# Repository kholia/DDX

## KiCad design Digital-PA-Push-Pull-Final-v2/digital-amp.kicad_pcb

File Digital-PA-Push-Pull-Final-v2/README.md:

# Digital-PA

A digital mode power amplifier for 160-10m.
Created using Kicad 8.x.

Licensed under Attribution-NonCommercial 4.0 (CC BY-NC 4.0).

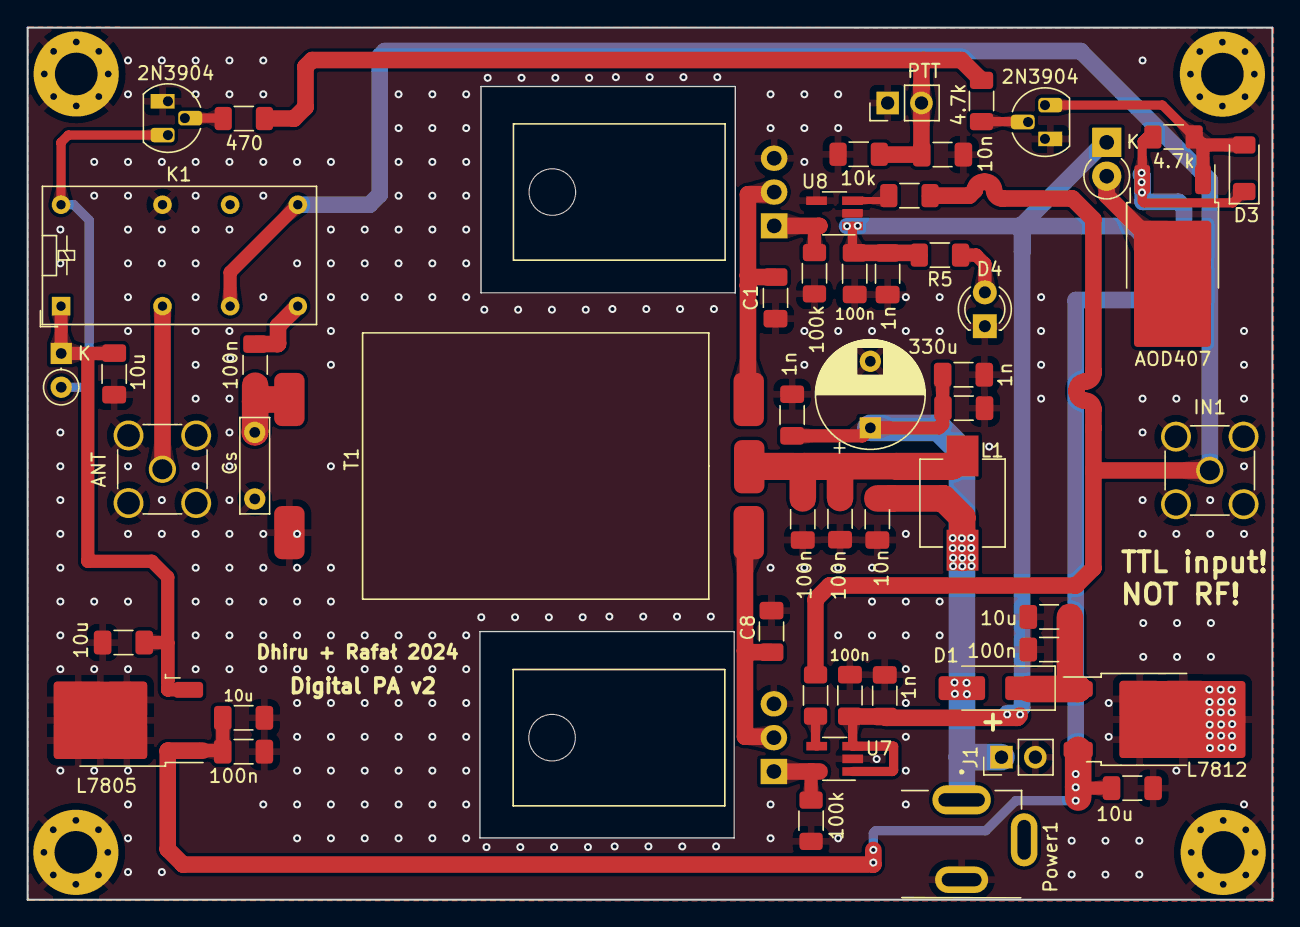
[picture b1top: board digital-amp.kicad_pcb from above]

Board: 2 copper layers, 93.5 x 65.5 mm, 58 parts (0 on the bottom side), 24 nets.

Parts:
B1, B2, B3, B4, B5: 100n; C_1206_3216Metric_Pad1.33x1.80mm_HandSolder
C1, C8: 100p; C_1206_3216Metric_Pad1.33x1.80mm_HandSolder
C2, C3, C5, C9, C11: 10u; C_1206_3216Metric_Pad1.33x1.80mm_HandSolder
C4, C6: 100n; C_1206_3216Metric_Pad1.33x1.80mm_HandSolder
C7: 330u; CP_Radial_D8.0mm_P5.00mm
C10: Cs; C_Rect_L7.0mm_W2.0mm_P5.00mm
C12, C13, C15, C17: 1n; C_1206_3216Metric_Pad1.33x1.80mm_HandSolder
C14, C16, C18: 10n; C_1206_3216Metric_Pad1.33x1.80mm_HandSolder
D1: SS54; D_SMA_Handsoldering
D2: 1N4148; D_DO-35_SOD27_P2.54mm_Vertical_KathodeUp
D3: 5.1V; D_MiniMELF
D4: LED_3mm; LED_D3.0mm
D5: 1N4007; D_DO-41_SOD81_P2.54mm_Vertical_KathodeUp
H1, H2, H3, H4: MountingHole_Pad; MountingHole_3.2mm_M3_Pad_Via
IN1: Conn_Coaxial; SMA_Amphenol_901-144_Vertical
J1: FAN; PinHeader_1x02_P2.54mm_Vertical
K1: Omron G5V-2 / OEN 46-05-2C; Relay_DPDT_Omron_G5V-2
L1: ASPI-0630LR-2R2; L_6.3x6.3_H3-Longer
PTT1: PTT; PinHeader_1x02_P2.54mm_Vertical
Power1: DC-005 (Barrel Jack); XKB_DC-005-5A-2.0_Modded
Q1: AOD407; TO-252-2-Mod
Q2, Q5: 2N3904; TO-92_HandSolder
Q3, Q4: IRF510; TO-220-3_Horizontal_TabDown
R1, R2: 100k; R_1206_3216Metric_Pad1.30x1.75mm_HandSolder
R3, R4: 4.7k; R_1206_3216Metric_Pad1.30x1.75mm_HandSolder
R5: 2k; R_1206_3216Metric_Pad1.30x1.75mm_HandSolder
R6: 470; R_1206_3216Metric_Pad1.30x1.75mm_HandSolder
R7: 10k; R_1206_3216Metric_Pad1.30x1.75mm_HandSolder
R8, R9: 3.3; R_1206_3216Metric_Pad1.30x1.75mm_HandSolder
RF1: ANT; SMA_Amphenol_901-144_Vertical
T1: BN-43-3312, 1T+1T:3T; BN-43-3312-Modded
U2: L7812; TO-252-2-Mod
U6: L7805; TO-252-2
U7, U8: UCC27517A; SOT-23-5_HandSoldering

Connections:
11.5V: B1.2, B2.2, C12.1, C13.1, D5.1 (K), R5.2, U7.1 (VDD), U7.3, U8.1 (VDD)
+5V: C3.1, C11.1, D2.1 (K), K1.1, U6.3 (OUT)
+12V: C2.1, C6.1, C9.1, D3.1 (K), Q1.3 (S), R3.1, U2.3 (OUT), U6.1 (IN)
+VDC: C7.1, C15.1, C16.1, C17.1, C18.1, D1.2 (A), J1.1, L1.2, Power1.1
ANTENNA: K1.4, RF1.1 (In)
GND: B1.1, B2.1, B3.1, B4.1, C1.1, C2.2, C3.2, C4.2, C5.2, C6.2, C7.2, C8.1, C9.2, C10.1, C11.2, C12.2, C13.2, C14.2, C15.2, C16.2, C17.2, C18.2, D4.1, H1.1, H2.1, H3.1, H4.1, IN1.2 (Ext), J1.2, K1.13, PTT1.1, Power1.2, Q2.1 (E), Q3.3 (S), Q4.3 (S), Q5.1 (E), R1.1, R2.1, R7.2, RF1.2 (Ext), T1.5 (S1), U2.2 (GND), U6.2 (GND), U7.2 (GND), U8.2 (GND), U8.4
unnamed: C4.1, C5.1, D1.1 (K), U2.1 (IN)
unnamed: D2.2 (A), K1.16, Q5.3 (C)
unnamed: D3.2 (A), Q1.1 (G), Q2.3 (C), R3.2
unnamed: D4.2, R5.1
unnamed: D5.2 (A), Q1.2 (D)
unnamed: Q2.2 (B), R4.1
unnamed: C1.2, Q3.2 (D), T1.1 (PR1)
unnamed: Q3.1 (G), R1.2, U8.5
unnamed: C8.2, Q4.2 (D), T1.3 (PR2)
unnamed: Q4.1 (G), R2.2, U7.5
unnamed: Q5.2 (B), R6.2
unnamed: R8.1, U8.3
unnamed: R9.1, U7.4
unnamed: B3.2, B4.2, L1.1, T1.2 (PM)
unnamed: B5.2, C10.2, T1.4 (S2)
PTT: C14.1, PTT1.2, R4.2, R6.1, R7.1
RF_OUT: B5.1, K1.8
Rig1: IN1.1 (In), K1.6, K1.9, R8.2, R9.2

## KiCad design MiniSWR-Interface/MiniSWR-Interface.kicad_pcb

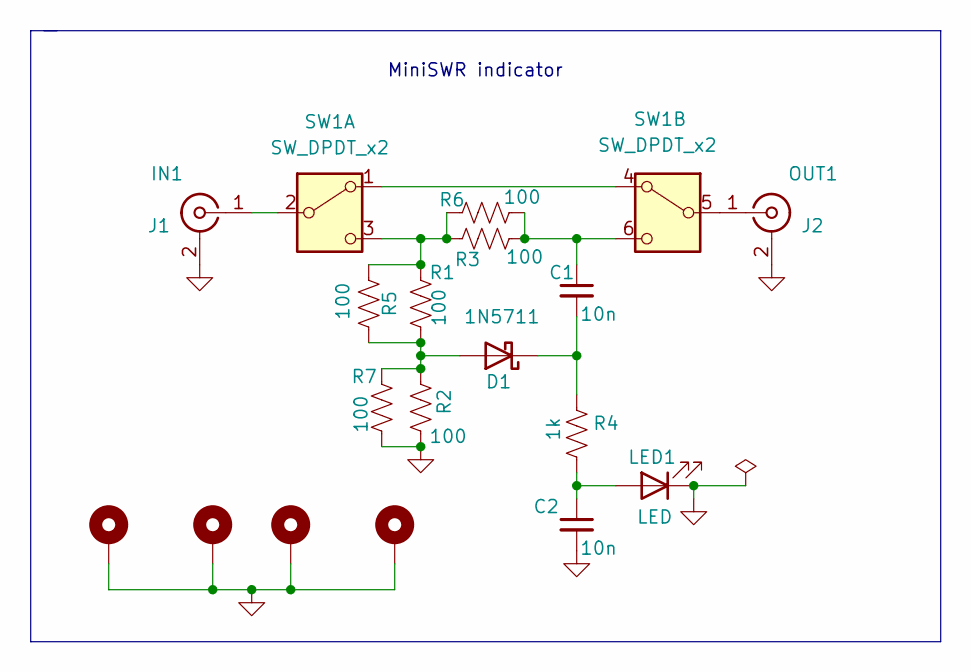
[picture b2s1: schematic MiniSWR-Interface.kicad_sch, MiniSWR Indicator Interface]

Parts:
C1, C2: 10n; C_1206_3216Metric_Pad1.33x1.80mm_HandSolder
D1: 1N5711; D_DO-35_SOD27_P7.62mm_Horizontal
H1, H2, H3, H4: MountingHole_Pad; MountingHole_2.2mm_M2_Pad_Via
J1: IN1; SMA_Samtec_SMA-J-P-X-ST-EM1_EdgeMount
J2: OUT1; SMA_Samtec_SMA-J-P-X-ST-EM1_EdgeMount
LED1: LED; LED_D3.0mm
R1, R2, R3, R5, R6, R7: 100; R_2512_6332Metric_Pad1.40x3.35mm_HandSolder
R4: 1k; R_1206_3216Metric_Pad1.30x1.75mm_HandSolder
SW1: SW_DPDT_x2; MTS-203 Switch

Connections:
GND: C2.2, H1.1, H2.1, H3.1, H4.1, J1.2 (Ext), J2.2 (Ext), LED1.1 (K), R2.1, R7.1
unnamed: D1.2 (A), R1.1, R2.2, R5.1, R7.2
unnamed: C1.2, D1.1 (K), R4.2
unnamed: J1.1 (In), SW1.2 (B)
unnamed: J2.1 (In), SW1.5 (B)
unnamed: C2.1, LED1.2 (A), R4.1
unnamed: SW1.1 (A), SW1.4 (A)
unnamed: R1.2, R3.1, R5.2, R6.1, SW1.3 (C)
unnamed: C1.1, R3.2, R6.2, SW1.6 (C)

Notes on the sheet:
MiniSWR indicator

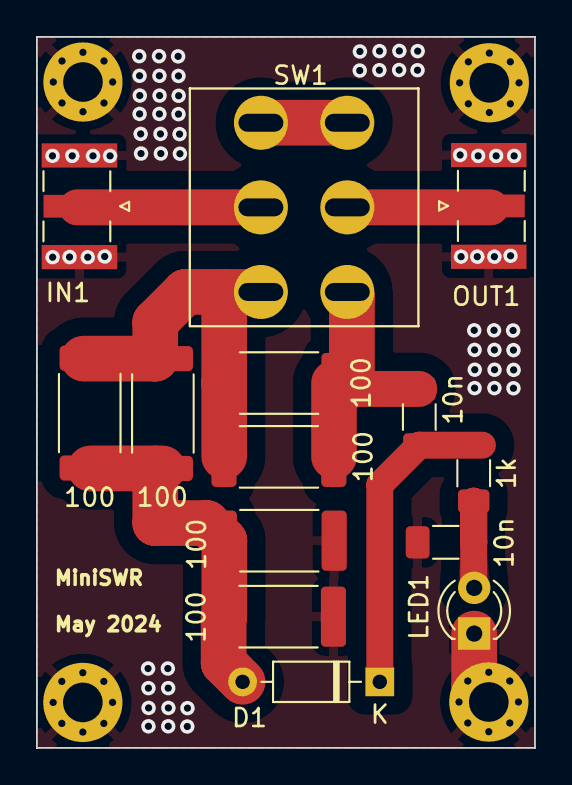
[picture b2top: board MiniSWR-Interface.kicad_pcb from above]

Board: 2 copper layers, 27.7 x 39.5 mm, 18 parts (0 on the bottom side), 9 nets.

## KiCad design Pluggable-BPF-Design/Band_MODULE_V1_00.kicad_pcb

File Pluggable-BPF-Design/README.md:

Usage: Open the KiCad schematic - all components have the exact datasheet
links. Use only high-quality SMD caps and inductors as prescribed.

Links:

- https://aa7ee.wordpress.com/2021/03/04/the-ve7bpo-direct-conversion-receiver-mainframe/

- https://vk3hn.wordpress.com/2021/02/27/sp-9-a-compact-five-band-ssb-cw-qrp-transceiver/

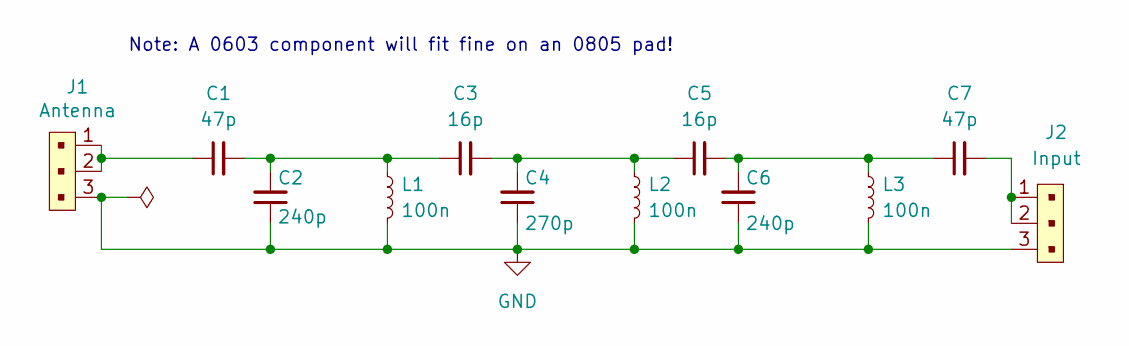
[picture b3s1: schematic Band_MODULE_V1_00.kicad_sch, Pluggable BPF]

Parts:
C1, C7: 47p; C_0805_2012Metric_Pad1.18x1.45mm_HandSolder
C2, C6: 240p; C_0805_2012Metric_Pad1.18x1.45mm_HandSolder
C3, C5: 16p; C_0805_2012Metric_Pad1.18x1.45mm_HandSolder
C4: 270p; C_0805_2012Metric_Pad1.18x1.45mm_HandSolder
J1: Antenna; PinHeader_1x3_P2.54mm_Drill1.02mm; MPN 0022232031; Digi-Key_PN WM4201-ND
J2: Input; PinHeader_1x3_P2.54mm_Drill1.02mm; MPN 0022232031; Digi-Key_PN WM4201-ND
L1, L2, L3: 100n; L_1210_3225Metric_Pad1.42x2.65mm_HandSolder

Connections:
GND: C2.1, C4.1, C6.1, J1.3, J2.3, L1.2, L2.2, L3.2
unnamed: C1.1, J1.1, J1.2
unnamed: C1.2, C2.2, C3.1, L1.1
unnamed: C3.2, C4.2, C5.1, L2.1
unnamed: C5.2, C6.2, C7.1, L3.1
unnamed: C7.2, J2.1, J2.2

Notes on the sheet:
Note: A 0603 component will fit fine on an 0805 pad!

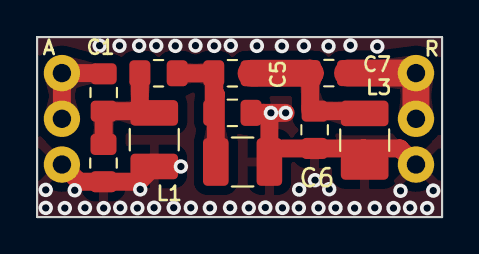
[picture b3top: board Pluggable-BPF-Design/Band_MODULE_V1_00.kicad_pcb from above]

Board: 2 copper layers, 22.5 x 10.0 mm, 12 parts (0 on the bottom side), 6 nets.

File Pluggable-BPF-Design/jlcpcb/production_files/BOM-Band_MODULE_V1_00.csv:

Comment,Designator,Footprint,LCSC
47p,"C1,C7",C_0805_2012Metric_Pad1.18x1.45mm_HandSolder,C14857
16p,"C3,C5",C_0805_2012Metric_Pad1.18x1.45mm_HandSolder,C152845
270p,C4,C_0805_2012Metric_Pad1.18x1.45mm_HandSolder,C501860
240p,"C2,C6",C_0805_2012Metric_Pad1.18x1.45mm_HandSolder,C520005
100n,"L1,L2,L3",L_1210_3225Metric_Pad1.42x2.65mm_HandSolder,C709637
Antenna,J1,PinHeader_1x3_P2.54mm_Drill1.02mm_Modded_2,
Input,J2,PinHeader_1x3_P2.54mm_Drill1.02mm_Modded_2,

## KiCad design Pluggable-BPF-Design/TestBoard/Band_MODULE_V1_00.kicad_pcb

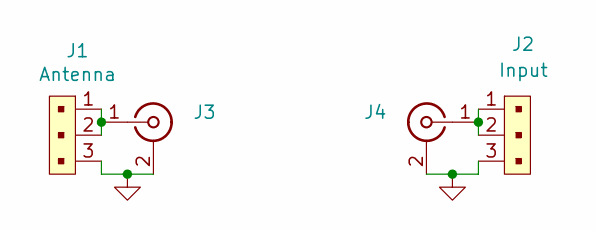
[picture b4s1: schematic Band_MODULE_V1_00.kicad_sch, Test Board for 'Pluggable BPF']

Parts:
J1: Antenna; PinHeader_1x3_P2.54mm_Drill1.02mm_Modded_2; MPN 0022232031; Digi-Key_PN WM4201-ND
J2: Input; PinHeader_1x3_P2.54mm_Drill1.02mm_Modded_2; MPN 0022232031; Digi-Key_PN WM4201-ND
J3, J4: Conn_Coaxial; SMA_Samtec_SMA-J-P-H-ST-EM1_EdgeMount

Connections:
GND: J1.3, J2.3, J3.2 (Ext), J4.2 (Ext)
unnamed: J1.1, J1.2, J3.1 (In)
unnamed: J2.1, J2.2, J4.1 (In)

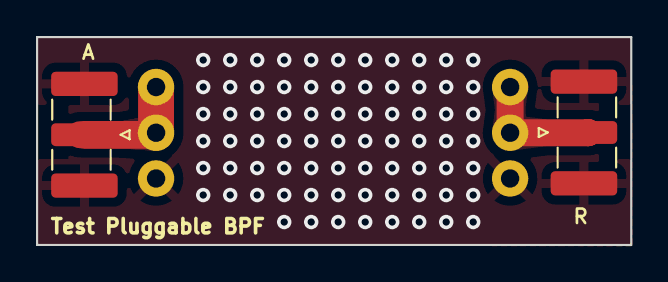
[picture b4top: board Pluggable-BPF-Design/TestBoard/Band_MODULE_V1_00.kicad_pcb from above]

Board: 2 copper layers, 33.0 x 11.6 mm, 4 parts (0 on the bottom side), 3 nets.
